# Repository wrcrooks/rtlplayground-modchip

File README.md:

# RTLPlayground mod chip

An RP2350 board inside SWTG024AS-V2.0 switches (MokerLink 2G040210GS, XikeStor SKS3200M-4GPY2XF) that
takes over management from the RTL8372's built-in 8051. The 8051 keeps only what has to run on it,
under a small bridge firmware, and tunnels the rest to the RP2350:

- chip init;
- SerDes and SFP upkeep;
- the CPU-port packet DMA;
- PHY, SerDes and flash access.

**Status:** Not tested as I haven't received the assembled PCBs yet.

The design, the link protocol, the pinouts and the mechanical constraints are in
[ARCHITECTURE.md](ARCHITECTURE.md). To test the firmware before the boards arrive, a Beetle RP2350 on jumper wires
stands in for the mod chip: [docs/beetle-test-rig.md](docs/beetle-test-rig.md).

| Path | What |
|---|---|
| `hardware/` | KiCad 10 schematic and 4-layer board, routed, with clean ERC and DRC. Also the board outline reaching headers T3, T8 and T5, a 1:1 print template, a DXF, photo overlays, STL/STEP for a printed fit check, JLCPCB production files, and the scripts that generate and check all of it. See [hardware/README.md](hardware/README.md) |
| `firmware/rp2350/` | The RP2350's application firmware in C (Pico SDK 2, lwIP): RTLPlayground's web UI, command line, IP stack, DHCP/DNS/NTP/syslog, STP/LACP/IGMP/LLDP and configuration, plus HTTPS, an SNMP agent and a graphs dashboard, with RTLPlayground's modules compiled unchanged from a submodule. Builds and passes host tests, not yet run on hardware. See [firmware/rp2350/README.md](firmware/rp2350/README.md) |
| `firmware/micropython/` | RP2350/RP2040 tools in MicroPython: `read_chip_id.py` reads the switch over T3, `bridge_link.py` is the host side of the bridge protocol, `bridge_host_test.py` talks to the bridge over T5, and `test_bridge_link.py` checks the protocol against the bridge's own frames |

The RP2350's application firmware is in `firmware/rp2350/`; it needs the submodule
(`git submodule update --init`).

## The bridge firmware

The 8051 side lives in RTLPlayground, on the `feat/modchip` branch of the fork:
[`modchip/bridge/`](https://github.com/wrcrooks/RTLPlayground/tree/feat/modchip/modchip/bridge). It shares
RTLPlayground's chip-level modules there. Build it from that repository's root:

```
make -f modchip/bridge/Makefile MACHINE=SWGT024_V2_0_UNMANAGED LAYOUT=compact   # MokerLink, 512 KiB
make -f modchip/bridge/Makefile MACHINE=SWGT024_V2_0_MANAGED                    # XikeStor, 2 MiB
```

## Rebuilding the hardware

Needs the KiCad 10 flatpak and a checkout of kicad-agent-kit:

```
KAK=~/Desktop/Workspace/KiCad/kicad-agent-kit hardware/build.sh
```

This goes from the schematic through ERC, layout, Freerouting, DRC and the JLCPCB files to the STL/STEP.

## Tests

```
make -C firmware/rp2350/test PICO_SDK_PATH=...   # framing, a simulated bridge, TLS, SNMP
python3 firmware/micropython/test_bridge_link.py
python3 hardware/check_sch.py         # ERC, and every pin's net against hardware/expected-nets.json
```

## Credits

- [vDorst/rtl-rs](https://github.com/vDorst/rtl-rs), by vDorst: a Rust library and CLI for the RTL837x's
  slave interface. Its I²C transactions are the reference for the firmware's register access over T3
  (`t3 on`, `t3 test`), above all the write format, which RTLPlayground's notes left open. It also
  shows that the PHY, SerDes and SFP engines can be reached through plain registers.

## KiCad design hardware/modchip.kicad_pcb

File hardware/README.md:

# Mod chip board outline

A single rigid board that mates with T3, T8 and T5 on an SWTG024AS-V2.0 and reaches the reset line at
D3. It avoids every through-hole or tall part and leaves the SPI flash U8 free for a test clip.

| File | What |
|---|---|
| `modchip.kicad_pcb`, `modchip.kicad_pro` | KiCad 10 board: the outline on Edge.Cuts, J1-J3 on the bottom side on the T3, T8 and T5 holes, TP1 above D3 for the reset wire to D3's anode, the switch's parts on Dwgs.User, U8's clip zone on Cmts.User. Aux and grid origin at T3 pin 1 |
| `make_pcb.py`, `finish.py`, `build.sh`, `modchip.kicad_dru` | Layout and routing pipeline (below), with JLCPCB's design rules |
| `modchip.kicad_sch`, `schematic.pdf` | KiCad 10 schematic of the whole mod chip, and a PDF of it |
| `make_sch.py`, `kisexpr.py` | Generate the schematic: every pin's net is listed in `make_sch.py` |
| `check_sch.py`, `expected-nets.json` | ERC, and KiCad's netlist compared pin by pin with the intended nets |
| `outline.py` | The outline, the header holes and the obstacles in one place. Running it checks the clearances and writes the files below |
| `modchip-outline.dxf` | Edge.Cuts, the header holes and the reset pad, in mm, origin at T3 pin 1, Y up |
| `modchip-outline.svg` | 1:1 template with the outline, holes, obstacles and the U8 clip zone |
| `overlay-managed.jpg` | The same drawn on the photo it is measured on: a managed board from [up-n-atom/SWTG118AS](https://github.com/up-n-atom/SWTG118AS/blob/main/photos/SWGT024AS-v2.0/SWTG024AS-v2-pcb-top.jpg) |
| `overlay.jpg` | The same on the unmanaged board's photo in RTLPlayground's `doc/devices/photos/`, as a cross-check |

Regenerate everything with:

```
python3 outline.py --photo SWTG024AS-v2-pcb-top.jpg --calibration managed   # downloaded from the link above
python3 outline.py --photo SWTG024AS-v2.0-top-uman.png   # from RTLPlayground doc/devices/photos/SWTG024AS-v2.0-unmanaged/
```

It exits non-zero if the outline comes closer than 1.2 mm to an obstacle or the U8 clip zone, or if a
header hole sits less than 1.5 mm from the edge.

## Schematic

`modchip.kicad_sch` is generated by `make_sch.py`, which lists the net of every pin of every part;
it refuses to write a schematic with a pin left unassigned. Nets are drawn as global labels on short
stubs at the pins, named as on the board (`SW_SCL`, `SW_U0TXD`, ...). The symbols come from KiCad 10's
standard library. To rebuild and check it:

```
flatpak run --command=python3 org.kicad.KiCad make_sch.py
flatpak run --command=kicad-cli org.kicad.KiCad sch upgrade modchip.kicad_sch
python3 check_sch.py
flatpak run --command=kicad-cli org.kicad.KiCad sch export pdf -o schematic.pdf modchip.kicad_sch
```

- **ERC.** One error, which is intended: the two LM66100 ideal diodes (U2, U3) both drive +3V3. That
  ORing of the switch's and USB's supplies is their job.
- **Netlist.** All 240 pins land on their intended nets (53 nets). A deliberately swapped label is
  caught.

**Circuit summary:**

- **MCU.** RP2354A.
- **Flash.** U5, a W25Q16JVUXIQ in USON-8, with its decoupling cap C19. Both are DNP: fit them only
  with an RP2350A (see below).
- **Core supply.** The core regulator per the RP2350 datasheet's figure 22: L1 3.3 µH, CIN, COUT,
  33 Ω / 4.7 µF on VREG_AVDD, and a second 4.7 µF at DVDD pin 23.
- **Clock and boot.** A 12 MHz crystal, BOOTSEL and RUN buttons, SWD pads and a status LED.
- **USB.** USB-C with ESD protection (USBLC6-2SC6), an AP2112K-3.3 regulator, and LM66100 ideal diodes
  ORing USB's 3.3 V with the switch's.
- **Sense.** A 100k/100k divider from the switch's 3.3 V to GP26.
- **Switch lines.** 100 Ω in series on every line, 4.7 kΩ I²C pull-ups to the switch's 3.3 V.
- **Reset.** A 2N7002 with 1 kΩ in series to TP1, and 100 kΩ holding its gate off at boot.

**RP2354A or RP2350A.** The two are the same chip in the same QFN-60 with the same pinout. The
RP2354A adds a W25Q16JV die inside the package, wired to the same six QSPI pads that reach the package
pins (RP2350 datasheet, section 14.3). So:

- **with an RP2354A**, leave U5 and C19 off. Fitting U5 would put two flash chips on QSPI_SS;
- **with an RP2350A**, fit them.

Nothing else changes; QSPI_IOVDD is 3.3 V either way, which the RP2354A requires. KiCad 10's design
variants (Schematic Setup → Variants) can record the choice. They're not set up here because the
generator doesn't write them.

**Board link.** `make_pcb.py` ties J1-J3 and TP1 on the board to their symbols here and copies their
fields. Tools → Update PCB from Schematic then adds the other 62 parts and changes nothing about those
four.

## KiCad board (layout and routing)

`modchip.kicad_pcb` is generated from the schematic. `build.sh` runs the whole pipeline and stops at the
first failure:

```
KAK=~/Desktop/Workspace/KiCad/kicad-agent-kit ./build.sh [freerouting passes]
```

It needs the KiCad 10 flatpak and a checkout of kicad-agent-kit, which supplies the board-from-netlist
build, auto-placement, escape rings, plane fanout, Freerouting (with its JRE) and the A* finisher. In
order:

1. **Schematic.** `make_sch.py`, `kicad-cli sch upgrade`, then `check_sch.py`: ERC clean, every pin
   on its intended net.
2. **Board.** `make_pcb.py`:
   - outline, plus J1-J3 and TP1 placed on the switch's holes, exactly;
   - hand placement of U1, the regulator, the clock, the debug pads, the flash and the series
     resistors, then auto-placement of the rest; the script refuses overlapping courtyards;
   - In1 GND plane, In2 split into +3V3 and a +1V1 region under U1;
   - locked hand routes for VREG_LX, VREG_AVDD and U1's 3.3 V trunk to CIN, then plane fanout.
3. **Routing.** Freerouting, with analytics and telemetry off on its command line.
4. **Finishing.** `finish.py` joins anything Freerouting left open, without ripping up other nets.
5. **Pours and checks.** `make_pcb.py --pour` adds the outer GND pours, then DRC and renders.

6. **Production.** `kak.sh jlc` writes `production/`.

Snapshots go in `build/`: `placed.kicad_pcb` before routing, `routed.kicad_pcb` after it.

**DRC.** The routed board has no DRC errors and no warnings, schematic parity included.

## 3D model for a printed fit check (`mechanical/`)

`modchip-no-headers.stl` and `.step` contain the board and every assembled part, without the headers
J1-J3 or the pads J5 and TP1. Coordinates are in mm from T3 pin 1.

- **Orientation.** The board's underside sits at z = 0 with nothing below it: print it bottom down on
  the bed, with no supports.
- **Size.** 106.2 × 37.2 mm overall. The board body is 1.0 mm thick, and the tallest part, U5 the
  SOIC-8, reaches z = 3.15.
- **Holes.** The header holes are cut through: 0.8 mm for T3/T8 and 1.0 mm for T5. Printed holes come
  out small, so open them with a drill or scale them up to slide the print over pins on the switch.
- **U1.** It uses the QFN-56 7×7 mm model, which has the same body; KiCad's library has no QFN-60
  model.

## JLCPCB production files (`production/`)

| File | What |
|---|---|
| `RTLPlayground_mod_chip_RP2350_A0.zip` | Gerbers for 4 copper layers, masks, paste, silkscreen, outline, and drill files |
| `bom.csv` | 19 lines, every one with an LCSC number |
| `positions.csv` | 48 parts, all on the top side |
| `designators.csv`, `netlist.ipc` | Designator list and IPC netlist, for JLC's checks |

**Ordering:**

- **Board.** 4 layers, 1.0 mm thick (the stack in ARCHITECTURE.md assumes 1.0), 0.2 mm minimum via
  drill, any colour.
- **Assembly.** PCBA on the top side only, with `bom.csv` and `positions.csv`.
- **Parts.** Basic parts throughout, except four Extended ones: RP2350A, LM66100, the AOTA inductor
  and the ABM8 crystal. ARCHITECTURE.md says why.
- **Not assembled.** The headers J1-J3 are hand-soldered. The SWD pads J5 and the reset pad TP1 are
  bare copper.
- **Check in JLC's preview.** The rotation of U1 (QFN-60), U5 (SOIC-8), U2 (SC-70-6), Y1 and L1. The
  Fabrication Toolkit applies JLC's rotation corrections, but these packages are the ones to look at.

## Where the numbers come from

**Source.** Everything is measured on up-n-atom's photo of a managed SWTG024AS-V2.0. It's taken
almost straight down, so it is close to a flat scan:

- **Scale.** 38.3 px/mm, from U8's 1.27 mm pin pitch (38.5) and T3's 2.0 mm pitch (38.1).
- **Accuracy.** About ±0.3 mm.
- **Cross-checks on the photo itself.** T5 measures 2.55 mm pitch and the board 130.3 × 88.7 mm. Tall
  parts sit squarely on their footprints, and the round capacitors fill their silkscreen circles.

**Earlier estimate.** A first pass used the unmanaged photo in RTLPlayground's `doc/devices/photos/`. That photo is taken
at an angle:

- tall parts lean outward;
- the board's depth stretches, to about 95 mm;
- the heatsink appears 1.6 mm further back than it is;
- the header holes come out 0.4-0.8 mm off;
- the rear-right standoff is hidden under C102.

`overlay.jpg` draws the current model on that photo: everything lands within that error.

**Variants.** The managed and unmanaged boards are the same PCB (SWTG024AS-V2.0-17452) and differ only
in fitted parts. The managed one has the reset button K1, T5 without pins, and a W25Q16JV (2 MiB) at
U8 in the same 208-mil SOIC-8 footprint.

## Before ordering a board

1. **Check the print scale.** Print `modchip-outline.svg` at 100 % (A4 landscape fits) and measure the
   50 mm scale bar.
2. **Lay the print on the switch.** Use the bare PCB, with the ports at the bottom of the page. Confirm
   that:
   - the holes fall on T3, T8 and T5;
   - the green outline clears J1, C124/C127, the 1R5 inductor, the heatsink, C102/EC1, the rear standoffs and the SFP cages;
   - the blue zone around U8 is free.
3. **Measure with calipers.** Do this on both switches, the MokerLink and the XikeStor:
   - the T3 pin 1 to T8 pin 6 distance (24.0 mm expected);
   - the T3 pin 1 to T5 pin 1 offset (94.2 mm across, 24.9 mm towards the front, expected);
   - the T5 pitch.
4. **Measure heights.** The lid's inside height over T3/T8 and over the tail, which needs at least
   about 9 mm.
5. **Update and rerun.** Put the measured positions into `outline.py`, run it again, then import the
   DXF into KiCad: File → Import → Graphics, layer Edge.Cuts, units mm.

If the two switches differ, or the tail's fit is too tight to rely on, cut the board at x ≈ 62 mm. That
leaves the main section over T3/T8 and the reset pad, about 39 × 17 mm, and T5 goes back to a 3-wire
harness.

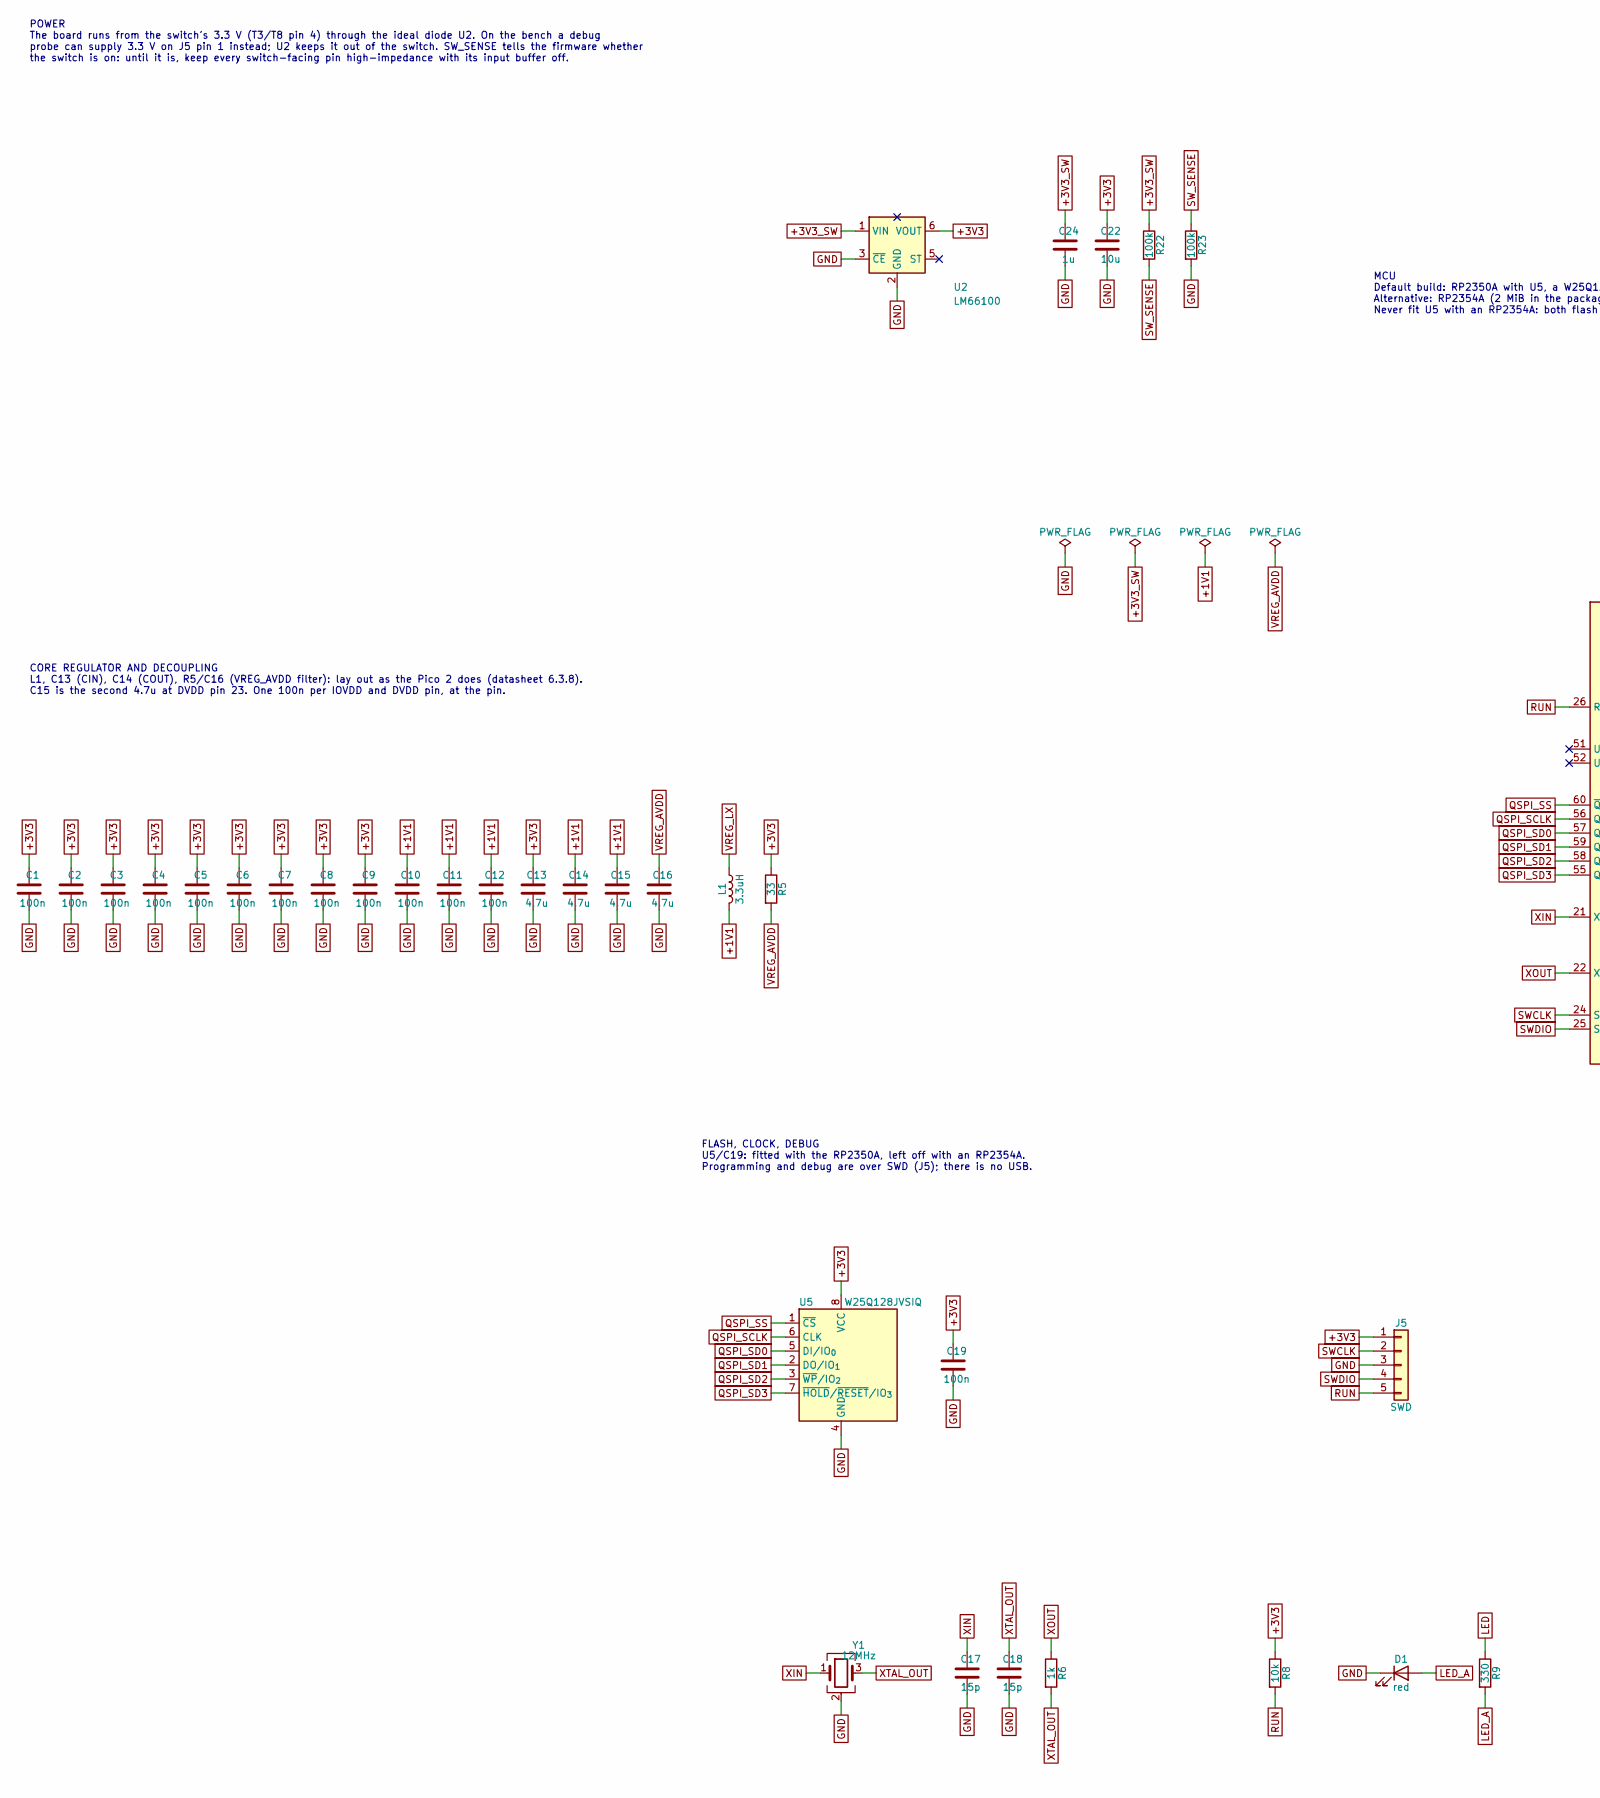
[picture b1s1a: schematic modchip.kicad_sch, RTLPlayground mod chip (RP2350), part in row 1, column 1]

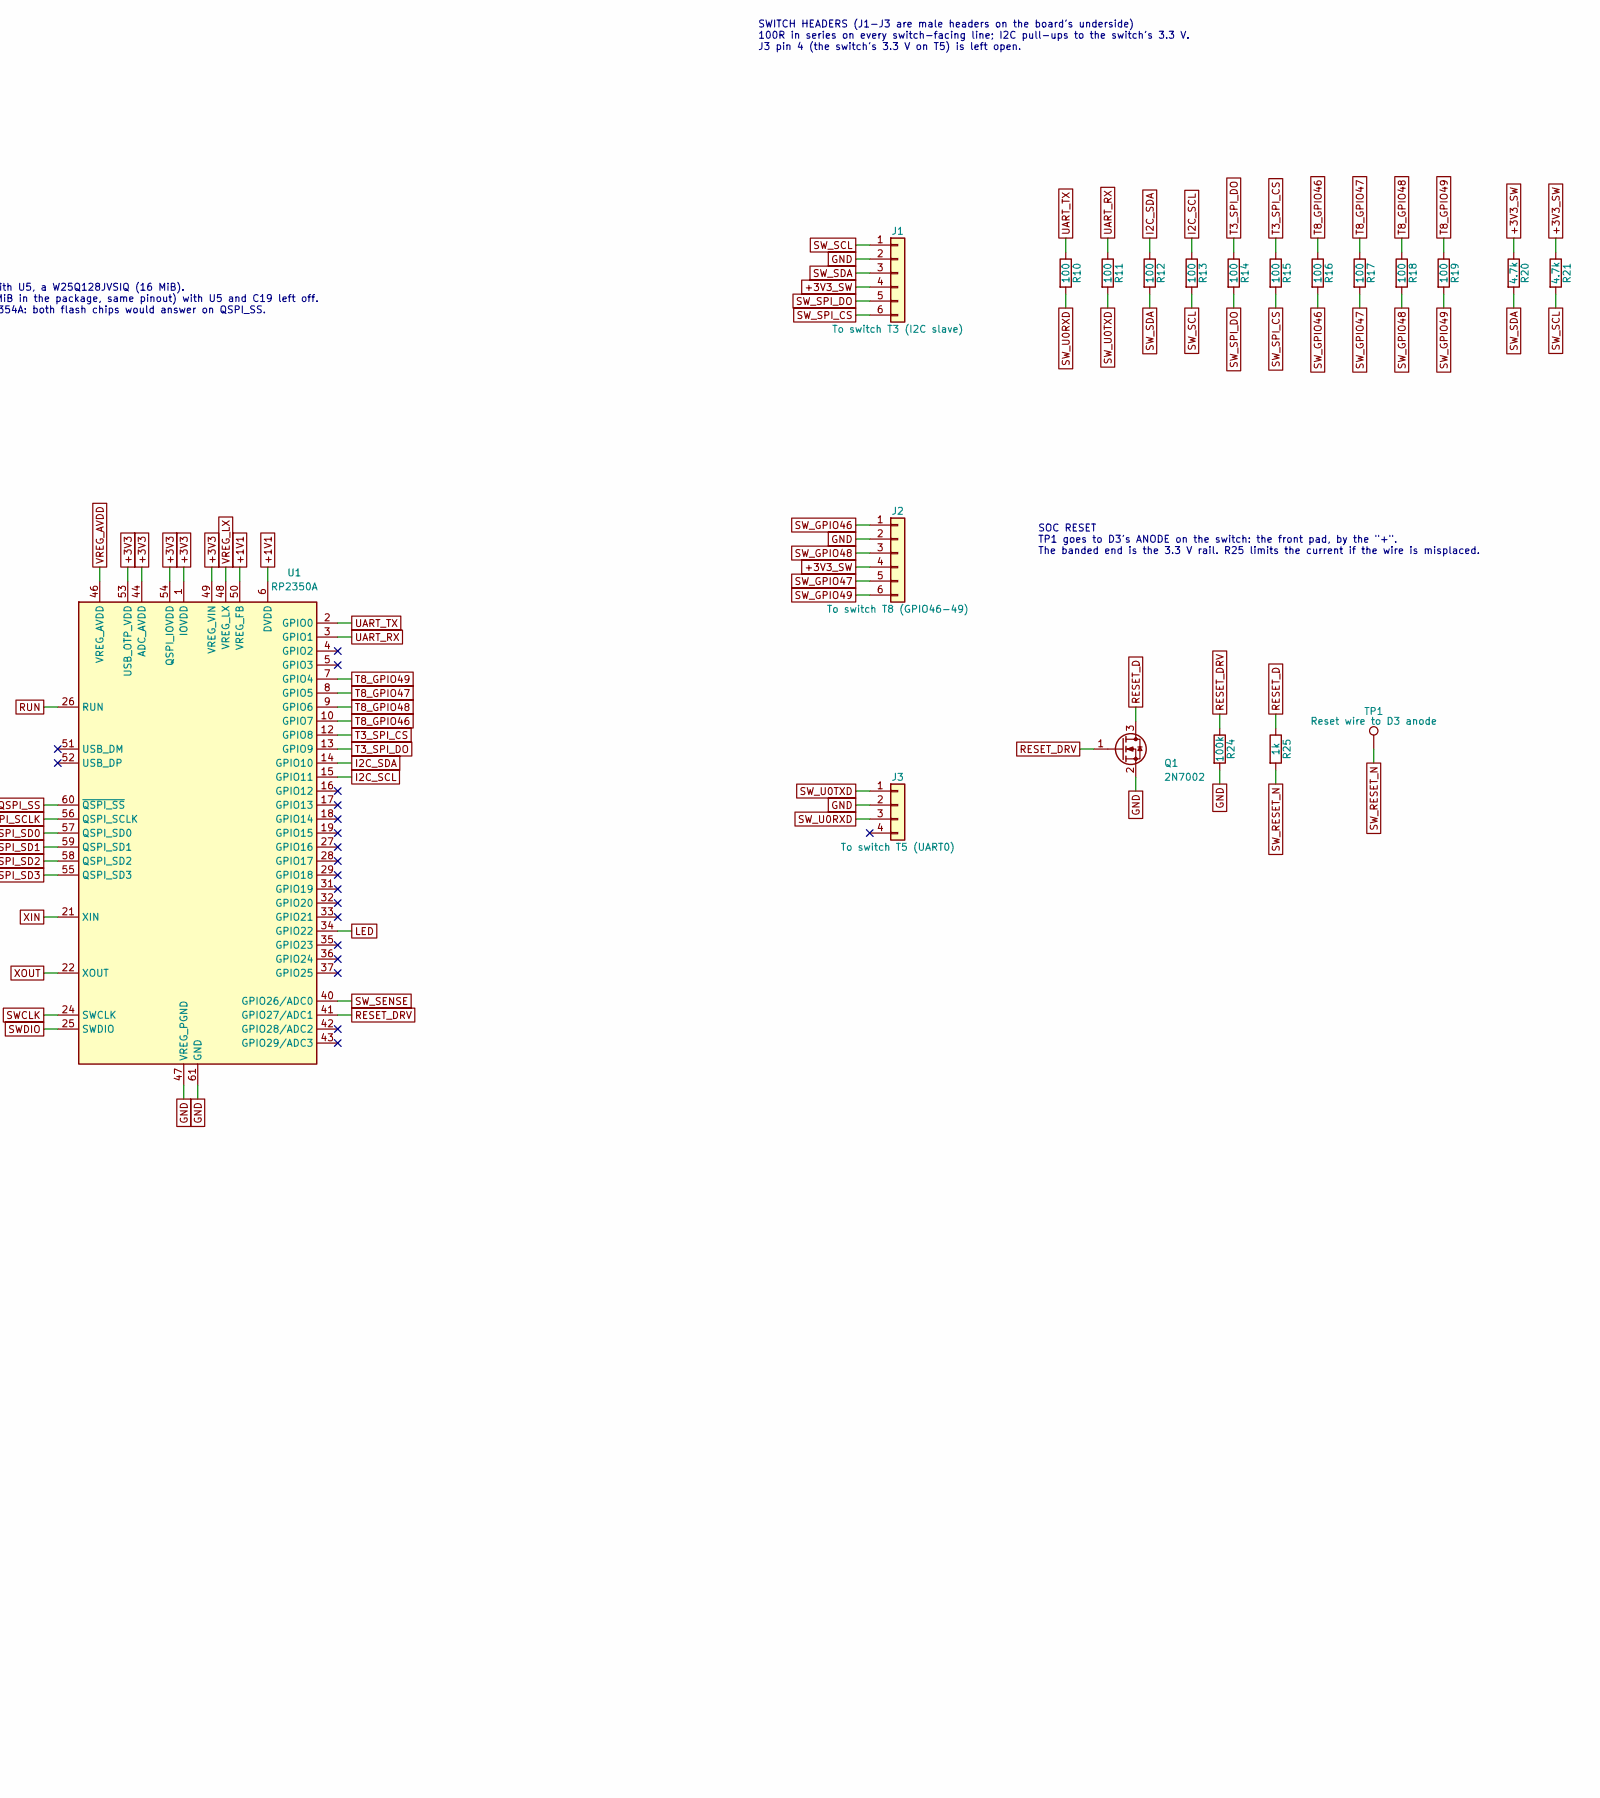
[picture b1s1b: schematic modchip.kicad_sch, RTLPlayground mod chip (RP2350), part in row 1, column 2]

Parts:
C1, C2, C3, C4, C5, C6, C7, C8, C9, C10, C11, C12, C19: 100n; C_0402_1005Metric; LCSC C1525
C13, C14, C15, C16: 4.7u; C_0402_1005Metric; LCSC C23733
C17, C18: 15p; C_0402_1005Metric; LCSC C1548
C22: 10u; C_0603_1608Metric; LCSC C19702
C24: 1u; C_0402_1005Metric; LCSC C52923
D1: red; LED_0603_1608Metric; LCSC C2286
J1: To switch T3 (I2C slave); PinHeader_1x06_P2.00mm_Vertical
J2: To switch T8 (GPIO46-49); PinHeader_1x06_P2.00mm_Vertical
J3: To switch T5 (UART0); PinHeader_1x04_P2.54mm_Vertical
J5: SWD; PinHeader_1x05_P1.27mm_Vertical
L1: 3.3uH; L_Murata_DFE201610P; MPN Abracon AOTA-B201610S3R3-101-T, the dat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; LCSC C42411119
Q1: 2N7002; SOT-23; LCSC C8545
R5: 33; R_0402_1005Metric; LCSC C25105
R6, R25: 1k; R_0402_1005Metric; LCSC C11702
R8: 10k; R_0402_1005Metric; LCSC C25744
R9: 330; R_0402_1005Metric; LCSC C25104
R10, R11, R12, R13, R14, R15, R16, R17, R18, R19: 100; R_0402_1005Metric; LCSC C25076
R20, R21: 4.7k; R_0402_1005Metric; LCSC C25900
R22, R23, R24: 100k; R_0402_1005Metric; LCSC C25741
TP1: Reset wire to D3 anode; TestPoint_THTPad_D1.5mm_Drill0.7mm
U1: RP2350A; QFN-60-1EP_7x7mm_P0.4mm_EP3.4x3.4mm_ThermalVias; LCSC C42411118
U2: LM66100; SOT-363_SC-70-6; LCSC C2869734
U5: W25Q128JVSIQ; SOIC-8_5.3x5.3mm_P1.27mm; LCSC C97521
Y1: 12MHz; Crystal_SMD_3225-4Pin_3.2x2.5mm; MPN Abracon ABM8-272-T3: the RP2350 is tune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; LCSC C20625731

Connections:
+1V1: C10.1, C11.1, C12.1, C14.1, C15.1, L1.2, U1.6 (DVDD), U1.23 (DVDD), U1.39 (DVDD), U1.50 (VREG_FB)
+3V3: C1.1, C2.1, C3.1, C4.1, C5.1, C6.1, C7.1, C8.1, C9.1, C13.1, C19.1, C22.1, J5.1, R5.1, R8.1, U1.1 (IOVDD), U1.11 (IOVDD), U1.20 (IOVDD), U1.30 (IOVDD), U1.38 (IOVDD), U1.44 (ADC_AVDD), U1.45 (IOVDD), U1.49 (VREG_VIN), U1.53 (USB_OTP_VDD), U1.54 (QSPI_IOVDD), U2.6 (VOUT), U5.8 (VCC)
+3V3_SW: C24.1, J1.4, J2.4, R20.1, R21.1, R22.1, U2.1 (VIN)
GND: C1.2, C2.2, C3.2, C4.2, C5.2, C6.2, C7.2, C8.2, C9.2, C10.2, C11.2, C12.2, C13.2, C14.2, C15.2, C16.2, C17.2, C18.2, C19.2, C22.2, C24.2, D1.1 (K), J1.2, J2.2, J3.2, J5.3, Q1.2 (S), R23.2, R24.2, U1.47 (VREG_PGND), U1.61 (GND), U2.2 (GND), U2.3 (~CE), U5.4 (GND), Y1.2 (G), Y1.4 (G)
I2C_SCL: R13.1, U1.15 (GPIO11)
I2C_SDA: R12.1, U1.14 (GPIO10)
LED: R9.1, U1.34 (GPIO22)
LED_A: D1.2 (A), R9.2
QSPI_SCLK: U1.56 (QSPI_SCLK), U5.6 (CLK)
QSPI_SD0: U1.57 (QSPI_SD0), U5.5 (DI/IO_{0})
QSPI_SD1: U1.59 (QSPI_SD1), U5.2 (DO/IO_{1})
QSPI_SD2: U1.58 (QSPI_SD2), U5.3 (~WP/IO_{2})
QSPI_SD3: U1.55 (QSPI_SD3), U5.7 (~HOLD/~RESET/IO_{3})
QSPI_SS: U1.60 (~QSPI_SS), U5.1 (~CS)
RESET_D: Q1.3 (D), R25.1
RESET_DRV: Q1.1 (G), R24.1, U1.41 (GPIO27/ADC1)
RUN: J5.5, R8.2, U1.26 (RUN)
SWCLK: J5.2, U1.24 (SWCLK)
SWDIO: J5.4, U1.25 (SWDIO)
SW_GPIO46: J2.1, R16.2
SW_GPIO47: J2.5, R17.2
SW_GPIO48: J2.3, R18.2
SW_GPIO49: J2.6, R19.2
SW_RESET_N: R25.2, TP1.1
SW_SCL: J1.1, R13.2, R21.2
SW_SDA: J1.3, R12.2, R20.2
SW_SENSE: R22.2, R23.1, U1.40 (GPIO26/ADC0)
SW_SPI_CS: J1.6, R15.2
SW_SPI_DO: J1.5, R14.2
SW_U0RXD: J3.3, R10.2
SW_U0TXD: J3.1, R11.2
T3_SPI_CS: R15.1, U1.12 (GPIO8)
T3_SPI_DO: R14.1, U1.13 (GPIO9)
T8_GPIO46: R16.1, U1.10 (GPIO7)
T8_GPIO47: R17.1, U1.8 (GPIO5)
T8_GPIO48: R18.1, U1.9 (GPIO6)
T8_GPIO49: R19.1, U1.7 (GPIO4)
UART_RX: R11.1, U1.3 (GPIO1)
UART_TX: R10.1, U1.2 (GPIO0)
VREG_AVDD: C16.1, R5.2, U1.46 (VREG_AVDD)
VREG_LX: L1.1, U1.48 (VREG_LX)
XIN: C17.1, U1.21 (XIN), Y1.1
XOUT: R6.1, U1.22 (XOUT)
XTAL_OUT: C18.1, R6.2, Y1.3

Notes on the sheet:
POWER The board runs from the switch's 3.3 V (T3/T8 pin 4) through the ideal diode U2. On the bench a debug probe can supply 3.3 V on J5 pin 1 instead; U2 keeps it out of the switch. SW_SENSE tells the firmware whether the switch is on: until it is, keep every switch-facing pin high-impedance with 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
MCU Default build: RP2350A with U5, a W25Q128JVSIQ (16 MiB). Alternative: RP2354A (2 MiB in the package, same pinout) with U5 and C19 left off. Never fit U5 with an RP2354A: both flash chips would answer on QSPI_SS.
SOC RESET TP1 goes to D3's ANODE on the switch: the front pad, by the "+". The banded end is the 3.3 V rail. R25 limits the current if the wire is misplaced.
FLASH, CLOCK, DEBUG U5/C19: fitted with the RP2350A, left off with an RP2354A. Programming and debug are over SWD (J5); there is no USB.
SWITCH HEADERS (J1-J3 are male headers on the board's underside) 100R in series on every switch-facing line; I2C pull-ups to the switch's 3.3 V. J3 pin 4 (the switch's 3.3 V on T5) is left open.
CORE REGULATOR AND DECOUPLING L1, C13 (CIN), C14 (COUT), R5/C16 (VREG_AVDD filter): lay out as the Pico 2 does (datasheet 6.3.8). C15 is the second 4.7u at DVDD pin 23. One 100n per IOVDD and DVDD pin, at the pin.

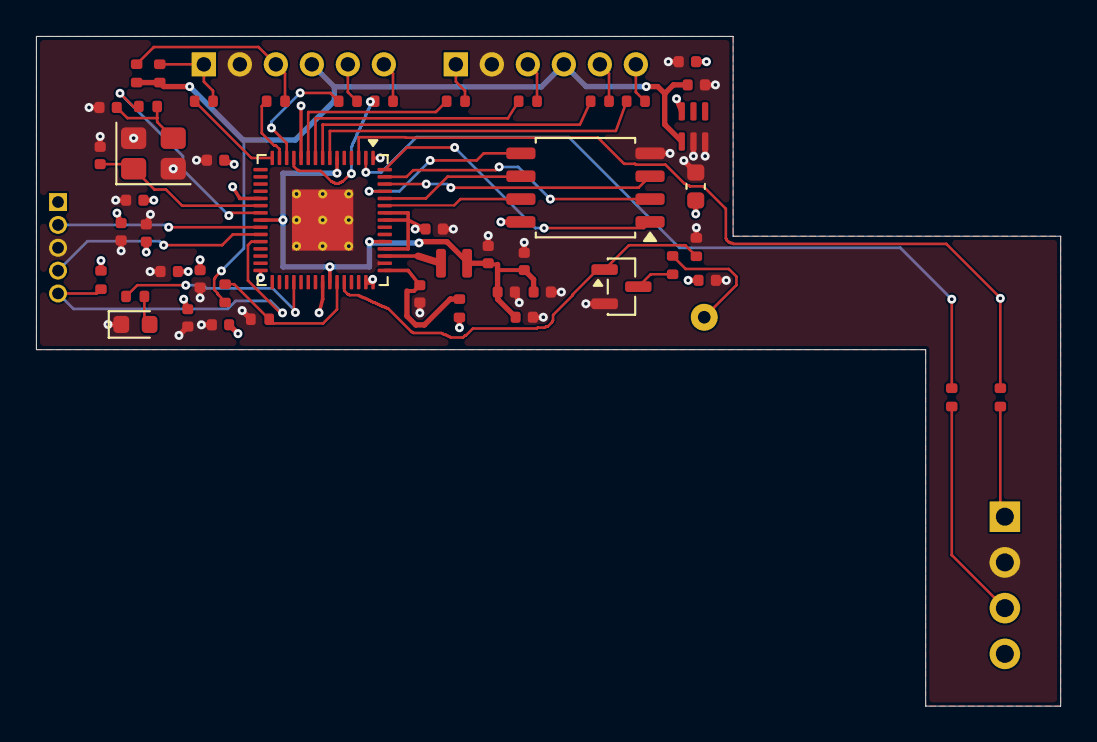
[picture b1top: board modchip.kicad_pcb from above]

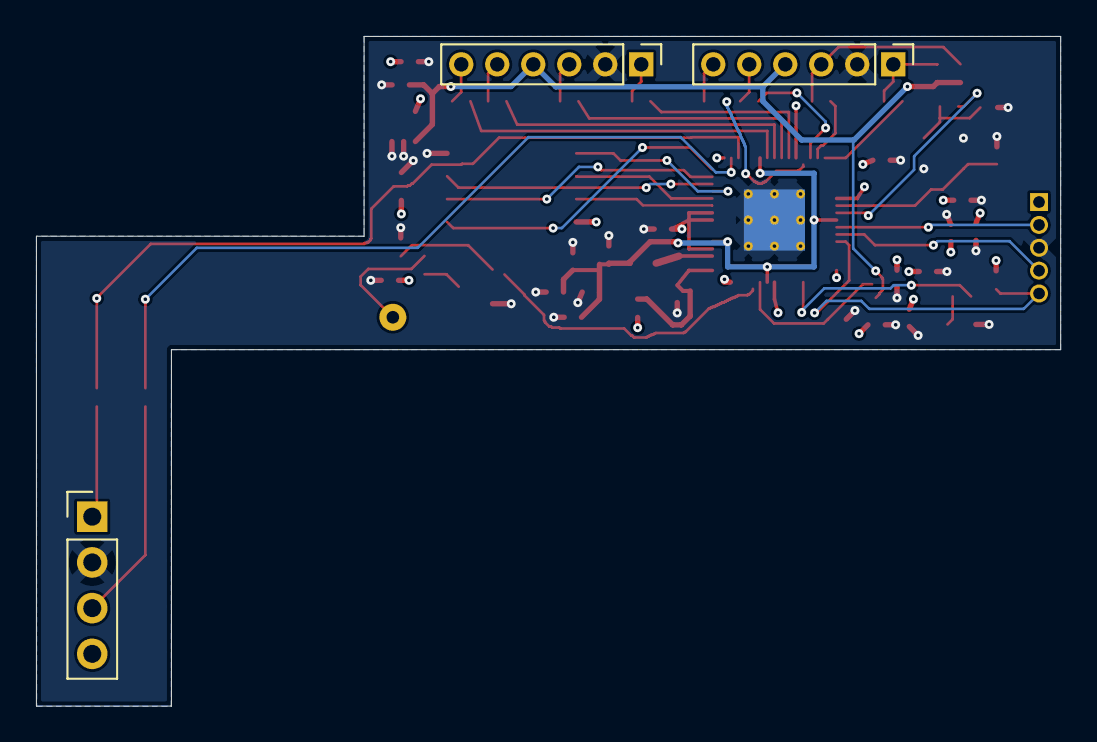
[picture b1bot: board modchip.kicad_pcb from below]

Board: 4 copper layers, 56.9 x 37.2 mm, 53 parts (3 on the bottom side), 44 nets.

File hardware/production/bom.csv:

Designator,Footprint,Quantity,Value,LCSC Part #
"C1, C10, C11, C12, C19, C2, C3, C4, C5, C6, C7, C8, C9",0402,13,100n,C1525
"C13, C14, C15, C16",0402,4,4.7u,C23733
"C17, C18",0402,2,15p,C1548
C22,0603,1,10u,C19702
C24,0402,1,1u,C52923
D1,0603,1,red,C2286
L1,L_Murata_DFE201610P,1,3.3uH,C42411119
Q1,SOT-23,1,2N7002,C8545
"R10, R11, R12, R13, R14, R15, R16, R17, R18, R19",0402,10,100,C25076
"R20, R21",0402,2,4.7k,C25900
"R22, R23, R24",0402,3,100k,C25741
"R25, R6",0402,2,1k,C11702
R5,0402,1,33,C25105
R8,0402,1,10k,C25744
R9,0402,1,330,C25104
U1,QFN-60-1EP_7x7mm_P0.4mm_EP3.4x3.4mm_ThermalVias,1,RP2350A,C42411118
U2,SOT-363_SC-70-6,1,LM66100,C2869734
U5,SOIC-8_5.3x5.3mm_P1.27mm,1,W25Q128JVSIQ,C97521
Y1,Crystal_SMD_3225-4Pin_3.2x2.5mm,1,12MHz,C20625731

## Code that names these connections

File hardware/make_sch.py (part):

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    # ---- Power: the switch's 3.3 V through an ideal diode, and the sense divider
    ox, oy = 10, 18
    s.text("POWER\nThe board runs from the switch's 3.3 V (T3/T8 pin 4) through the ideal diode U2. On the bench a debug\n"
           "probe can supply 3.3 V on J5 pin 1 instead; U2 keeps it out of the switch. SW_SENSE tells the firmware whether\n"
           "the switch is on: until it is, keep every switch-facing pin high-impedance with its input buffer off.",
           (ox, oy - 8))
    for ref, src, row in (("U2", "+3V3_SW", 8),):
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        "~{QSPI_SS}": "QSPI_SS", "QSPI_SCLK": "QSPI_SCLK", "QSPI_SD0": "QSPI_SD0", "QSPI_SD1": "QSPI_SD1",
        "QSPI_SD2": "QSPI_SD2", "QSPI_SD3": "QSPI_SD3",
        # GP11..GP4 face T3/T8 in header order once U1 is rotated 270 on the board
        "GPIO0": "UART_TX", "GPIO1": "UART_RX", "GPIO11": "I2C_SCL", "GPIO10": "I2C_SDA",
        "GPIO9": "T3_SPI_DO", "GPIO8": "T3_SPI_CS",
        "GPIO7": "T8_GPIO46", "GPIO6": "T8_GPIO48", "GPIO5": "T8_GPIO47", "GPIO4": "T8_GPIO49",
        "GPIO27/ADC1": "RESET_DRV", "GPIO22": "LED", "GPIO26/ADC0": "SW_SENSE",
        **{"GPIO%d" % n: None for n in (2, 3, 12, 13, 14, 15, 16, 17, 18, 19, 20, 21, 23, 24, 25)},
        "GPIO28/ADC2": None, "GPIO29/ADC3": None,
    })
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           "Connector_PinHeader_2.00mm:PinHeader_1x06_P2.00mm_Vertical", in_bom=False,
           fields={"Note": "Hand-soldered on the bottom side; not assembled (JLC: C22438289 if wanted)"})
    s.part("J2", "Connector_Generic:Conn_01x06", "To switch T8 (GPIO46-49)", (ox + 10, oy + 30),
           {"1": "SW_GPIO46", "2": "GND", "3": "SW_GPIO48", "4": "+3V3_SW", "5": "SW_GPIO47", "6": "SW_GPIO49"},
           "Connector_PinHeader_2.00mm:PinHeader_1x06_P2.00mm_Vertical", in_bom=False,
           fields={"Note": "Hand-soldered on the bottom side; not assembled (JLC: C22438289 if wanted)"})
    s.part("J3", "Connector_Generic:Conn_01x04", "To switch T5 (UART0)", (ox + 10, oy + 48),
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    series = [("R10", "UART_TX", "SW_U0RXD"), ("R11", "UART_RX", "SW_U0TXD"),
              ("R12", "I2C_SDA", "SW_SDA"), ("R13", "I2C_SCL", "SW_SCL"),
              ("R14", "T3_SPI_DO", "SW_SPI_DO"), ("R15", "T3_SPI_CS", "SW_SPI_CS"),
              ("R16", "T8_GPIO46", "SW_GPIO46"), ("R17", "T8_GPIO47", "SW_GPIO47"),
              ("R18", "T8_GPIO48", "SW_GPIO48"), ("R19", "T8_GPIO49", "SW_GPIO49")]
    for i, (ref, a, b) in enumerate(series):
        s.part(ref, R, "100", (ox + 22 + 3 * i, oy + 10), {"1": a, "2": b}, R0402)
    s.part("R20", R, "4.7k", (ox + 54, oy + 10), {"1": "+3V3_SW", "2": "SW_SDA"}, R0402, fields={"Near": "J1"})
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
